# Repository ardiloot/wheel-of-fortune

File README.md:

# Wheel of Fortune

## Overview

An over-engineered DIY version of Wheel of Fortune (Wheel or Prizes). The main features are:
* 3 LED strips with individually controllable LEDs (WLED)
* 3 linear servo motors for displaying effect logos
* absolute position optical encoder for wheel position (position depended effects)
* Amplified sound system for theme and effect sound
* ESP32 based LED and servo motor controller
* Orange PI 3 LTS based compute unit
* Node (React + Mantine) app for configuration
* Server stack for metrics, monitoring and backup

Outlook:

Internals:

Services:

For detailed instructions how to build the system, see following readme files:

1. [Mechanical setup](hw/mech)
1. [Electrical setup](hw/electrical)
1. [Embedded software](embedded_software)
1. [Server software](server)

## Development

Code is split to two main parts:
1. [Python backend](wheel_of_fortune) (FastAPI)
1. [Node frontend](wheel_of_fortune/frontend) (React + Mantine)

Finally, frontend static HTML + Javascript files are backed into backend Python package and served via backend FastAPI server. 

### Backend

#### Development environment

Python 3.11 is currently preferred, but should also work on any Python >= 3.10

```bash
python -m venv venv
source venv/bin/activate
pip install -r dev-requirements.txt
pip install -e .
```

#### Running backend

```bash
source venv/bin/activate
python -m wheel_of_fortune
```

#### Updating requirements

After adding dependency update requirement files by running:

```bash
source venv/bin/activate
pip-compile --upgrade -o requirements.txt pyproject.toml \
    && pip-compile --extra dev --upgrade -o dev-requirements.txt pyproject.toml \
    && pip-sync dev-requirements.txt
```

### Frontend

#### Setup development environment

Install `nvm` and `node` and install dependencies:

```bash
cd wheel_of_fortune/frontend/
curl -o- https://raw.githubusercontent.com/nvm-sh/nvm/v0.39.4/install.sh | bash
source ~/.bashrc
nvm install
nvm use
npm ci
```

#### Developer mode

Create `.env.local` file for overriding environment:

```bash
VITE_API_URL=https://wheel.int.example.com/api/v1
VITE_WS_URL=wss://wheel.int.example.com/api/v1/ws
```

Run frontend in `dev` mode:

```bash
nvm use
npm run dev
```

#### Release build

```bash
nvm use
npm run build
```

#### Update packages

To update `package-lock.json` and install updates:

```bash
npm update
npm install
```

To also update `package.json` file:

```bash
npm install -g npm-check-updates
ncu -u
npm install
```

### Build steps

Usually not needed, as [Github actions](tree/main/.github/workflows) automatically build and test frontend & docker images. But for completeness, here are commands to do build manually:

#### Frontend

```bash
cd wheel_of_fortune/frontend/
nvm use
npm ci
npm run build
cd ../..
```

#### Backend

```bash
python -m build
```

#### Docker image

```bash
docker build -t wheel_of_fortune .
```

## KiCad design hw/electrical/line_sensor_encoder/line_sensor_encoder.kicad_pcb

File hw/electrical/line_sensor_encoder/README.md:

## Line sensor encoder

Back                                        |  Front
:------------------------------------------:|:------------------------------------------:
  |  

Custom encoder PCB for detecting absolute position of the wheel.
It consists of 5 `TCRT5000L` line sensors combined with voltage comparators
to have five binary outputs.

[PDF schematic](line_sensor_encoder.pdf)

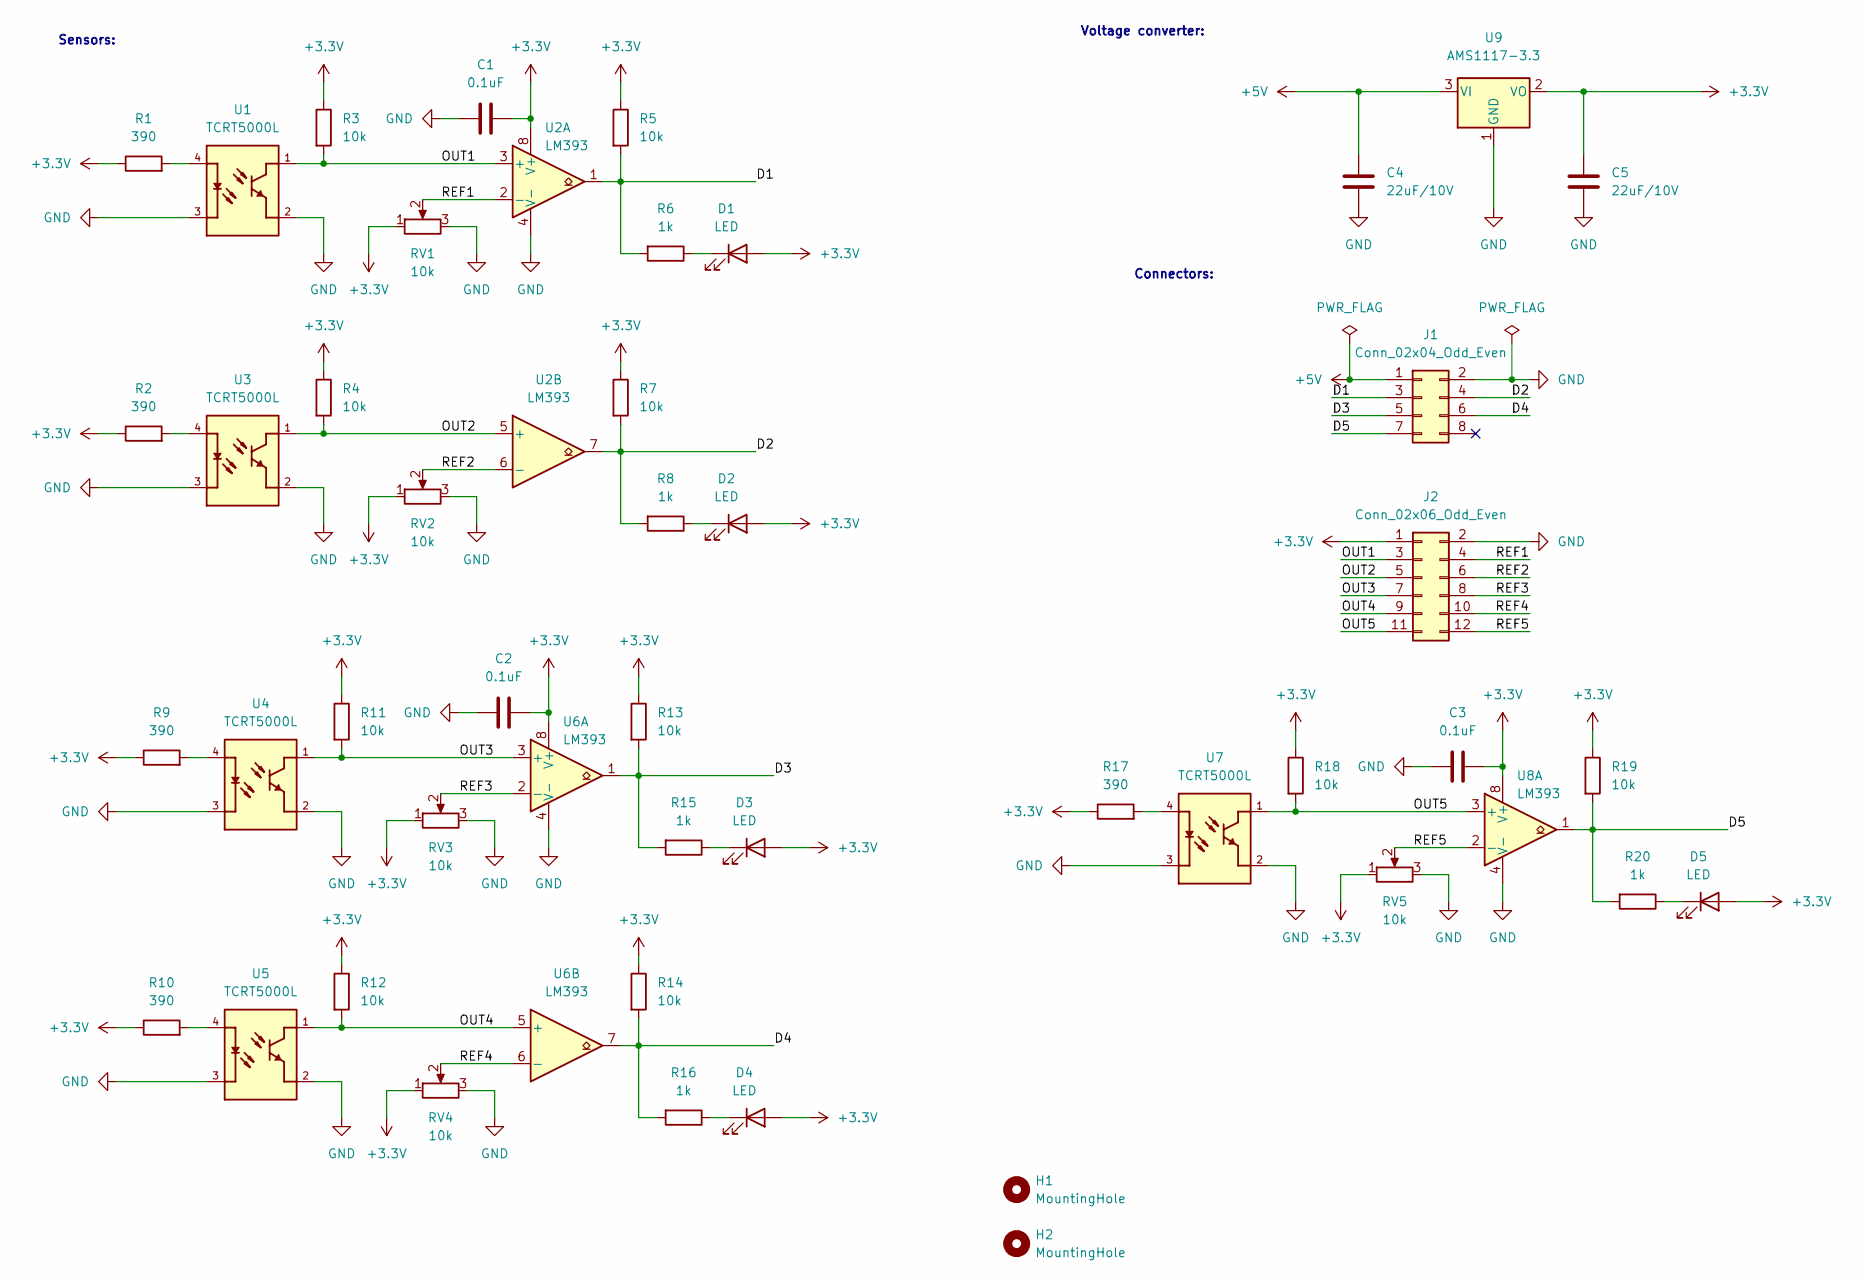
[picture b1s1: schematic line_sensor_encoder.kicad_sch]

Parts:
C1, C2, C3: 0.1uF; C_0805_2012Metric_Pad1.18x1.45mm_HandSolder
C4, C5: 22uF/10V; C_0805_2012Metric_Pad1.18x1.45mm_HandSolder
D1, D2, D3, D4, D5: LED; LED_0805_2012Metric_Pad1.15x1.40mm_HandSolder
H1, H2: MountingHole; MountingHole_3.2mm_M3_DIN965
J1: Conn_02x04_Odd_Even; PinHeader_2x04_P2.54mm_Vertical
J2: Conn_02x06_Odd_Even; PinHeader_2x06_P2.54mm_Vertical
R1, R2, R9, R10, R17: 390; R_0805_2012Metric_Pad1.20x1.40mm_HandSolder
R3, R4, R5, R7, R11, R12, R13, R14, R18, R19: 10k; R_0805_2012Metric_Pad1.20x1.40mm_HandSolder
R6, R8, R15, R16, R20: 1k; R_0805_2012Metric_Pad1.20x1.40mm_HandSolder
RV1, RV2, RV3, RV4, RV5: 10k; Potentiometer_Bourns_3296W_Vertical
U1, U3, U4, U5, U7: TCRT5000L; XDCR_TCRT5000L
U2, U6, U8: LM393; SOP-8_5.28x5.23mm_P1.27mm
U9: AMS1117-3.3; SOT-223-3_TabPin2

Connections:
+3.3V: C1.2, C2.2, C3.2, C5.1, D1.2 (A), D2.2 (A), D3.2 (A), D4.2 (A), D5.2 (A), J2.1, R1.1, R2.1, R3.1, R4.1, R5.1, R7.1, R9.1, R10.1, R11.1, R12.1, R13.1, R14.1, R17.1, R18.1, R19.1, RV1.1, RV2.1, RV3.1, RV4.1, RV5.1, U2.8 (V+), U6.8 (V+), U8.8 (V+), U9.2 (VO)
+5V: C4.1, J1.1, U9.3 (VI)
/D1: J1.3, R5.2, R6.2, U2.1
/D2: J1.4, R7.2, R8.2, U2.7
/D3: J1.5, R13.2, R15.2, U6.1
/D4: J1.6, R14.2, R16.2, U6.7
/D5: J1.7, R19.2, R20.2, U8.1
/OUT1: J2.3, R3.2, U1.1, U2.3 (+)
/OUT2: J2.5, R4.2, U2.5 (+), U3.1
/OUT3: J2.7, R11.2, U4.1, U6.3 (+)
/OUT4: J2.9, R12.2, U5.1, U6.5 (+)
/OUT5: J2.11, R18.2, U7.1, U8.3 (+)
/REF1: J2.4, RV1.2, U2.2 (-)
/REF2: J2.6, RV2.2, U2.6 (-)
/REF3: J2.8, RV3.2, U6.2 (-)
/REF4: J2.10, RV4.2, U6.6 (-)
/REF5: J2.12, RV5.2, U8.2 (-)
GND: C1.1, C2.1, C3.1, C4.2, C5.2, J1.2, J2.2, RV1.3, RV2.3, RV3.3, RV4.3, RV5.3, U1.2, U1.3, U2.4 (V-), U3.2, U3.3, U4.2, U4.3, U5.2, U5.3, U6.4 (V-), U7.2, U7.3, U8.4 (V-), U9.1 (GND)
unnamed: D1.1 (K), R6.1
unnamed: D2.1 (K), R8.1
unnamed: D3.1 (K), R15.1
unnamed: D4.1 (K), R16.1
unnamed: D5.1 (K), R20.1
unnamed: R1.2, U1.4
unnamed: R2.2, U3.4
unnamed: R9.2, U4.4
unnamed: R10.2, U5.4
unnamed: R17.2, U7.4

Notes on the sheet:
Sensors:
Connectors:
Voltage converter:

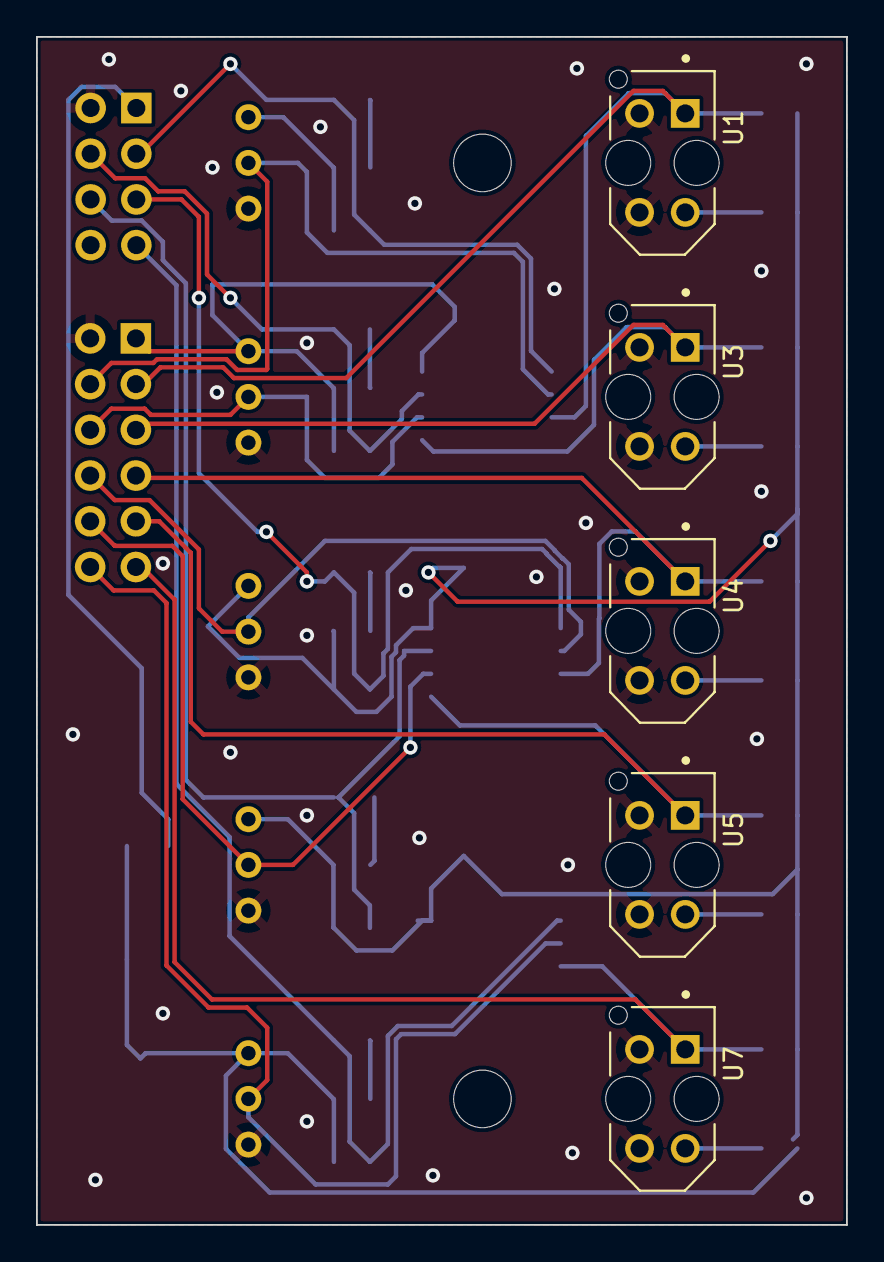
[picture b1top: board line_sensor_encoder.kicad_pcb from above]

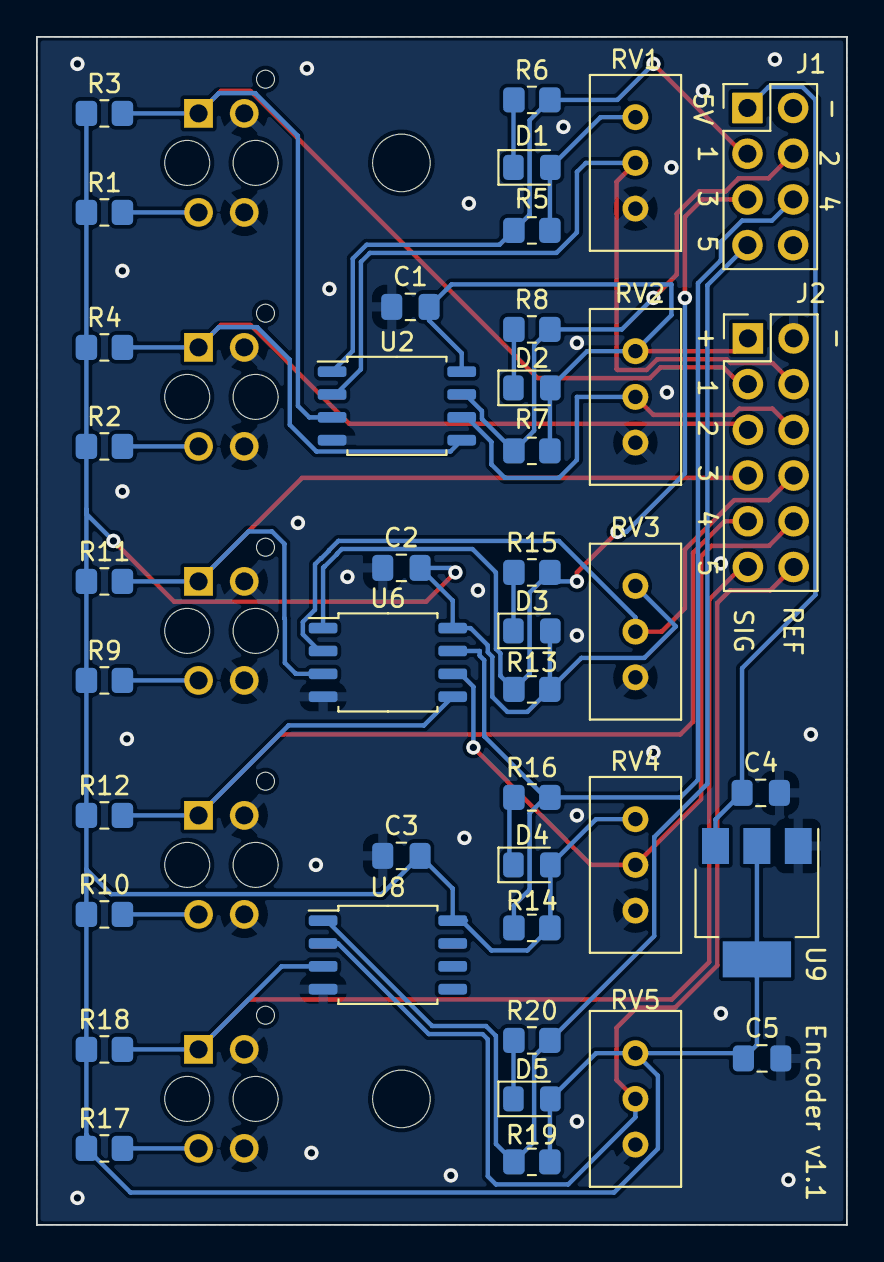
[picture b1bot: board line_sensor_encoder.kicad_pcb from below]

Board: 2 copper layers, 45.0 x 66.0 mm, 48 parts (43 on the bottom side), 28 nets.

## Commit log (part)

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2023-08-30 added display name config
2023-08-30 use display name
2023-08-30 fix readme and docker file
2023-08-31 configured code formatter and linter
2023-08-31 fixed lint errors
2023-08-31 updated plugins
2023-08-31 prettier fixes
2023-08-31 updated requirements
2023-08-31 added black formatter
2023-08-31 format fixes
2023-08-31 added missing pylance extension
2023-08-31 fix line length
2023-08-31 added icons for themes and effects
2023-08-31 remove esp32c3dev
2023-08-31 added startup and poweroff sounds
2023-08-31 better ws error handling
2023-08-31 fix wheel position
2023-08-31 added possibility to activate servos per effect
2023-09-01 independent sliders for volume channels
2023-09-01 report winning sector name
2023-09-01 less logging
2023-09-01 log client names
2023-09-01 changed to info
2023-09-01 cleaned up logging
2023-09-01 cleaned up logging 2
2023-09-02 added pinout sheet
2023-09-02 added pdf preview
2023-09-02 added wiring diagram
2023-09-02 encoder pattern
2023-09-02 line encoder
2023-09-02 added 3.3V dc converter
2023-09-02 added title block
2023-09-02 added small readme
2023-09-02 updated wiring diagram
2023-09-02 readme placeholder
2023-09-02 added drawings for amplifier
2023-09-02 amplifier assembly
2023-09-02 helper script to rotate STL files
2023-09-02 rotated STL files
2023-09-02 fix file name
2023-09-02 compute models
2023-09-02 correct folder
2023-09-02 fix orientation
2023-09-02 added dc converter models
2023-09-02 added encoder
2023-09-02 added limit wheel assembly
2023-09-02 mains relay assembly
2023-09-02 power switch assembly
2023-09-02 linear actuator
2023-09-02 cover subassembly
2023-09-02 wheel subassembly
2023-09-02 updated pattern
2023-09-02 added flipper subassembly
2023-09-02 speaker subassembly
2023-09-02 moved pattern under mech
2023-09-03 fix servo config
2023-09-03 tun servo speed
2023-09-03 sound system fixes
2023-09-03 play startup sound on main channel
2023-09-03 increased standstill timeout
2023-09-03 adjust timings
2023-09-03 increased log interval
2023-09-03 command line arguments for convert sounds script
2023-09-03 improved effect timing
2023-09-03 a bit more time to startup
2023-09-03 small tuning
2023-09-04 rudimentary orangepi setup instructions
2023-09-04 fix typos
2023-09-04 allow access to gpio through default group (1000)
2023-09-04 added bit more readme
2023-09-04 small readme addition
2023-09-04 more instructions
2023-09-04 cleanup instructions
2023-09-04 fix link
2023-09-04 specified Orange PI model
2023-09-04 updated server readme
2023-09-04 use zone.ee domain by default
2023-09-04 added instructions for vpn setup
2023-09-05 added info about promtail setup
2023-09-05 fixes for setup
2023-09-05 added internal domain
2023-09-05 added different startup dependencies for vpn and promtail
2023-09-06 send docker logs to journald
2023-09-06 small readme fix
2023-09-08 added venv and python3-dev instructions
2023-09-08 exclude unnecessary files from sdist
2023-09-08 added warning if frontend path does not exists
2023-09-08 fixes for servo motors
2023-09-08 small improvements
2023-09-08 warn -> warning
2023-09-08 upgrade traefik version
2023-09-08 clip sounds to 60 seconds
2023-09-08 bugfix
2023-09-08 use wav for faster startup
2023-09-08 fix for fast theme song fadeout
2023-09-08 remove some internal async functions
2023-09-08 added missing delay
2023-09-08 fix typo
2023-09-08 release 0.1.7
2023-09-08 changed defaults
2023-09-09 removed ping causing fatal error if connection to influxdb fails
2023-09-09 added backup file and safeguard against using settings before open()
2023-09-10 added more 3D models
2023-09-10 added backplate assembly
2023-09-10 support list of theme sounds
2023-09-10 document 3D printer settings
2023-09-10 less frequent pattern
2023-09-10 added renovate
2023-09-10 disable schedule
2023-09-10 Update docker/login-action digest to a5609cb
2023-09-10 Update docker/metadata-action digest to 79f06a3
2023-09-10 upgraded frontend packages
2023-09-10 Update actions/checkout action to v4
2023-09-10 Update actions/download-artifact action to v3
2023-09-10 Update actions/upload-artifact action to v3
2023-09-10 Update dependency build to v1
2023-09-10 enable renovate only for docker and ci
2023-09-10 enable renovate only for docker and ci 2
2023-09-10 re-added schedule
2023-09-10 upgraded python requirements
2023-09-14 Update docker/setup-qemu-action action to v3
2023-09-15 updated readme for electrical connections
2023-09-15 added spellcheck words
2023-09-15 added image for backlight leds
2023-09-15 rearranged sections
2023-09-15 formatting fix
2023-09-16 Update docker/login-action digest to b4bedf8
2023-09-16 Update docker/metadata-action digest to 879dcbb
2023-09-16 Update docker/build-push-action action to v5
2023-09-16 Update docker/setup-buildx-action action to v3
2023-09-17 added drawings for backplate and wheel
2023-09-17 added bom
2023-09-17 starter readme for mech design
2023-09-17 reorganized readme
2023-09-17 format fix
2023-09-17 added placeholders
2023-09-18 added info about limit wheels
2023-09-18 rename files
2023-09-18 added some more instructions
2023-09-18 moved bom to separate directory
2023-09-18 fix wrong directory
2023-10-11 support structured input sounds folder
2023-10-11 updated default servo pos
2023-10-13 catch all telemetry reporting errors
2023-10-13 added check for full queue
2023-10-13 standby state
2023-10-13 option to set state
2023-10-13 added debug lines
2023-10-13 cancel all maintain tasks if one fails/is cancelled
2023-10-13 test volume slider with quick response
2023-10-13 report servo mount pos
2023-10-15 added instructions for kopia
2023-10-15 readme how to setup kopia
2023-10-15 add default led transition value
2023-10-15 updated node to 20.8.1
2023-10-15 updated node lock file
2023-10-15 instructions to update lock file only
2023-10-15 more smooth volume / brightness sliders
2023-10-15 rudimentary support for servos
2023-10-15 improved shutdown logic
2023-10-15 removed unused code
2023-10-15 prepare for release
2023-10-15 fix transition units
2023-10-15 tuned transition length
2023-10-15 downgrade node
2023-10-17 added standby_timer
2023-10-17 negative values disable standby mode
2023-10-17 support led transitions
2023-10-17 more fixes
2023-10-17 update schemas
2023-10-17 larger slider buttons
2023-10-17 cleanup
2023-10-17 reworked servo page
2023-10-17 add leds transition
2023-10-17 added support for logo files
2023-10-17 separated logo to a file
2023-10-17 bugfixes
2023-10-17 add missing logo names
2023-10-17 added support for logo name
2023-10-17 add logos path
2023-10-17 more generic local www path
2023-10-17 add debugging
2023-10-17 test different mount order
2023-10-17 remove trailing /
2023-10-17 remove debug lines
2023-10-18 moved logos
2023-10-18 support local paths
2023-10-18 fix default logo location
2023-10-18 removed some debugging
2023-10-18 show version
2023-10-18 remove logo url
2023-10-18 cleanup readme
2023-11-17 Update docker/login-action digest to 3d58c27
2023-12-02 Update Node.js to v21
2023-12-04 Update docker/metadata-action digest to 31cebac
2023-12-09 Update actions/setup-python action to v5
2023-12-15 added more info about kopia
2023-12-15 use versions instead of hashes
2023-12-15 disable major and minor updates for dockerfile
2023-12-16 Update actions/download-artifact action to v4
2023-12-16 Update actions/upload-artifact action to v4
2023-12-17 decreased standstill timeout to 2 seconds
2023-12-17 added a bit of logging
2023-12-22 updated dev readme
2023-12-22 added a small overview
2023-12-22 smaller fixes
2023-12-22 added images
2023-12-31 added image of services
2023-12-31 try to fix links
2023-12-31 added image titles
2023-12-31 fix links
2024-01-20 Update actions/cache action to v4
2024-03-09 Update softprops/action-gh-release action to v2
2024-04-13 Update grafana/promtail Docker tag to v3
2024-05-24 Update grafana/loki Docker tag to v3
2024-05-24 Updated to WLED 0.14.4
2024-06-18 Update traefik Docker tag to v3
2024-06-22 Update docker/build-push-action action to v6
2024-06-25 Update grafana/grafana Docker tag to v11
2024-10-10 do not allow effect to be interrupted
2024-10-10 reduce standstill timeout to 1 second
2024-10-10 fix for wled compile error
2024-10-10 change renovate schedule
2024-10-12 add grafana email config
2024-10-19 allow high speeds spins interrupt playing effect
2025-06-17 Update grafana/grafana Docker tag to v12
2026-04-26 Migrate config renovate.json
2026-04-26 Update actions/cache action to v5
2026-04-26 Update actions/checkout action to v6
2026-04-26 Update actions/setup-python action to v6
2026-04-26 Update docker/build-push-action action to v7
2026-04-26 Update docker/login-action action to v4
2026-04-26 Update docker/metadata-action action to v6
2026-04-26 Update docker/setup-buildx-action action to v4
2026-04-26 Update docker/setup-qemu-action action to v4
2026-04-26 Update GitHub Artifact Actions
2026-04-26 Update grafana/grafana Docker tag to v13
2026-04-26 Update softprops/action-gh-release action to v3
2026-04-26 Update ghcr.io/linuxserver/librespeed Docker tag to v6
